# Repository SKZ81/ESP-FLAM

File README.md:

This is branch **master** (normal operation firmware)

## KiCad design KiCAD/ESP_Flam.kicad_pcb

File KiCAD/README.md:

# ESP FLAM PCB

## Top Layer

## Bottom Layer

## 3D View

## Real Board

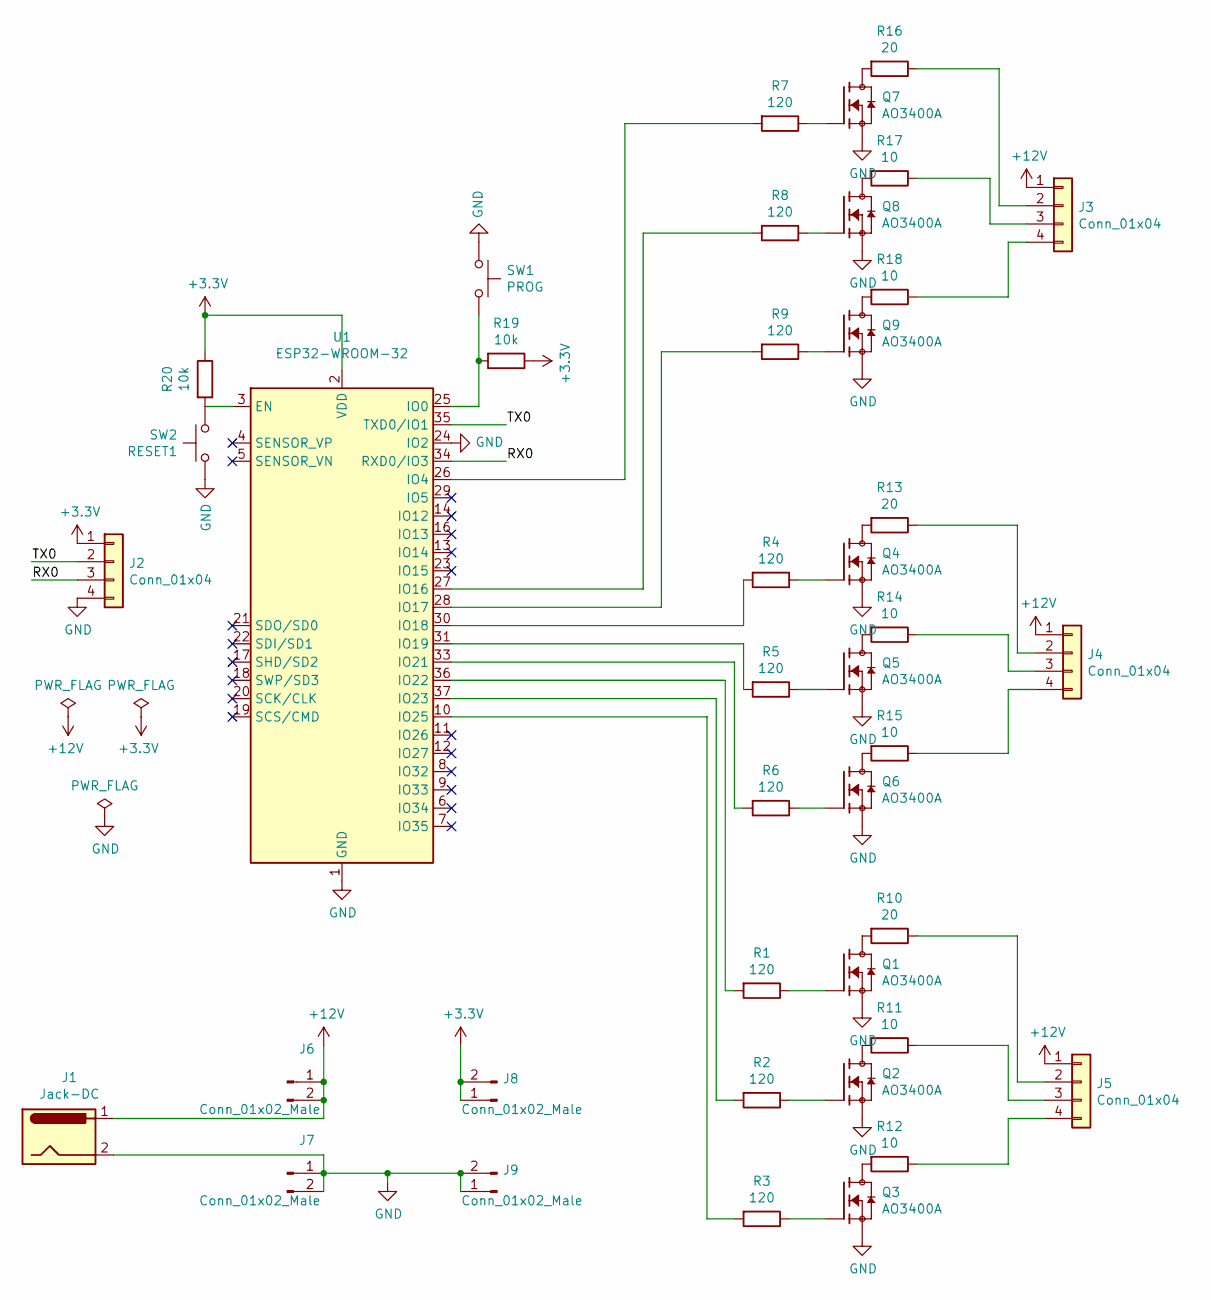
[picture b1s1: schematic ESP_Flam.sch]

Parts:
J1: Jack-DC; BarrelJack_CUI_PJ-063AH_Horizontal
J2, J3, J4, J5: Conn_01x04; PinHeader_1x04_P2.54mm_Vertical
J6, J7, J8, J9: Conn_01x02_Male; PinHeader_1x02_P2.54mm_Vertical
Q1, Q2, Q3, Q4, Q5, Q6, Q7, Q8, Q9: AO3400A; SOT95P280X125-3N; LCSC Part C347475
R1, R2, R3, R4, R5, R6, R7, R8, R9: 120; R_0805_2012Metric; LCSC Part C17437
R10, R13, R16: 20; R_Axial_DIN0414_L11.9mm_D4.5mm_P15.24mm_Horizontal
R11, R12, R14, R15, R17, R18: 10; R_Axial_DIN0414_L11.9mm_D4.5mm_P15.24mm_Horizontal
R19, R20: 10k; R_0805_2012Metric; LCSC Part C17414
RESET1: SW2; SW_PUSH_6mm
SW1: PROG; SW_PUSH_6mm
U1: ESP32-WROOM-32

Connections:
+3V3: J2.1, J8.1, J8.2, R19.1, R20.1, U1.2 (VDD)
+12V: J1.1, J3.1, J4.1, J5.1, J6.1, J6.2
/RX0: J2.3, U1.34 (RXD0/IO3)
/TX0: J2.2, U1.35 (TXD0/IO1)
GND: J1.2, J2.4, J7.1, J7.2, J9.1, J9.2, Q1.2 (S), Q2.2 (S), Q3.2 (S), Q4.2 (S), Q5.2 (S), Q6.2 (S), Q7.2 (S), Q8.2 (S), Q9.2 (S), RESET1.1, SW1.1, U1.1 (GND), U1.15 (GND), U1.24 (IO2), U1.38 (GND), U1.39 (GND)
unnamed: J3.2, R16.1
unnamed: J3.3, R17.1
unnamed: J3.4, R18.1
unnamed: J4.2, R13.1
unnamed: J4.3, R14.1
unnamed: J4.4, R15.1
unnamed: J5.2, R10.1
unnamed: J5.3, R11.1
unnamed: J5.4, R12.1
unnamed: Q1.1 (G), R1.1
unnamed: Q1.3 (D), R10.2
unnamed: Q2.1 (G), R2.1
unnamed: Q2.3 (D), R11.2
unnamed: Q3.1 (G), R3.1
unnamed: Q3.3 (D), R12.2
unnamed: Q4.1 (G), R4.1
unnamed: Q4.3 (D), R13.2
unnamed: Q5.1 (G), R5.1
unnamed: Q5.3 (D), R14.2
unnamed: Q6.1 (G), R6.1
unnamed: Q6.3 (D), R15.2
unnamed: Q7.1 (G), R7.1
unnamed: Q7.3 (D), R16.2
unnamed: Q8.1 (G), R8.1
unnamed: Q8.3 (D), R17.2
unnamed: Q9.1 (G), R9.1
unnamed: Q9.3 (D), R18.2
unnamed: R1.2, U1.36 (IO22)
unnamed: R2.2, U1.37 (IO23)
unnamed: R3.2, U1.10 (IO25)
unnamed: R4.2, U1.30 (IO18)
unnamed: R5.2, U1.31 (IO19)
unnamed: R6.2, U1.33 (IO21)
unnamed: R7.2, U1.26 (IO4)
unnamed: R8.2, U1.27 (IO16)
unnamed: R9.2, U1.28 (IO17)
unnamed: R19.2, SW1.2, U1.25 (IO0)
unnamed: R20.2, RESET1.2, U1.3 (EN)

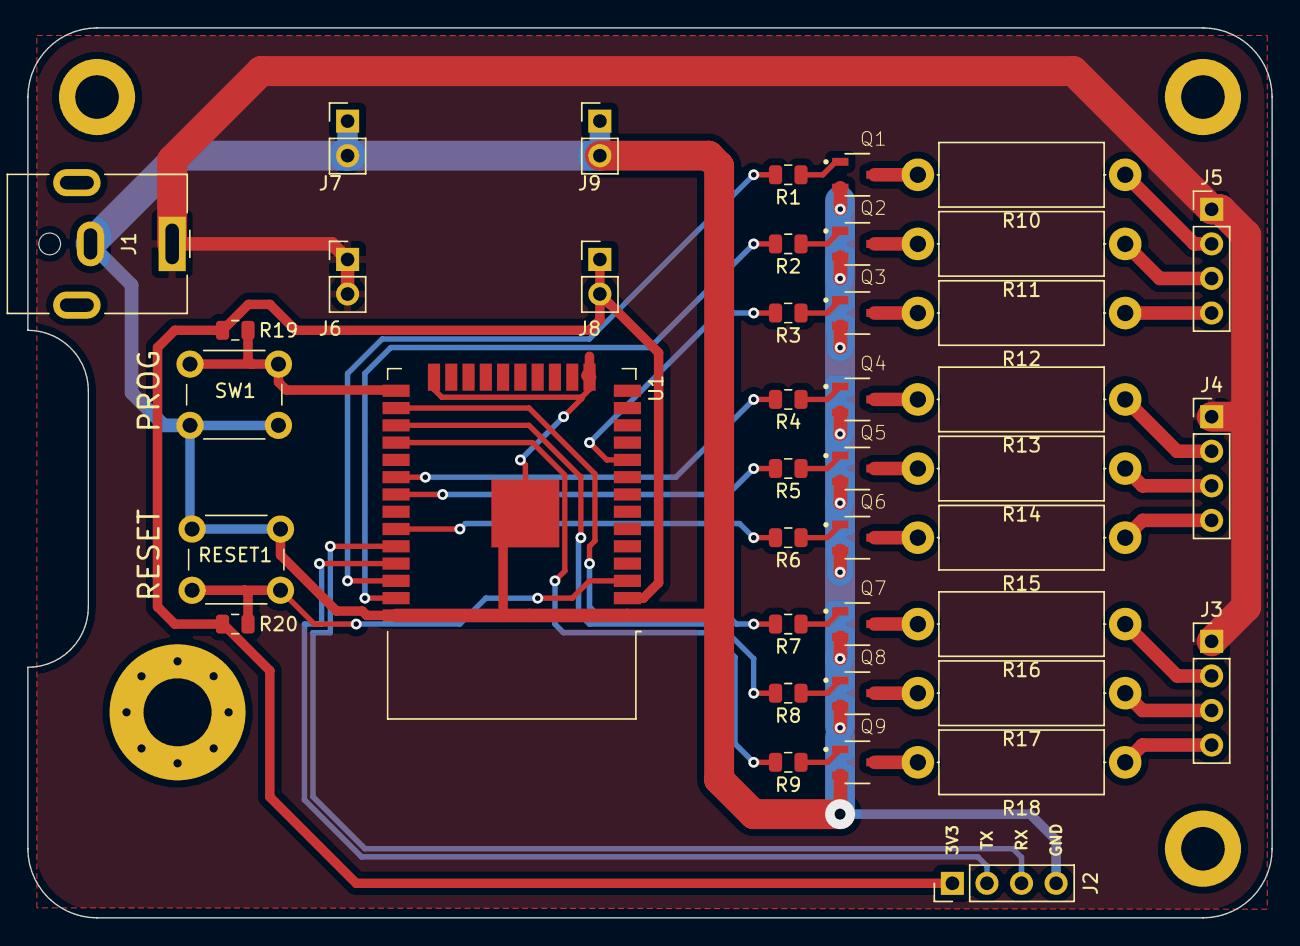
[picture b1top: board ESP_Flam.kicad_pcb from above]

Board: 2 copper layers, 91.4 x 65.4 mm, 44 parts (0 on the bottom side), 43 nets.

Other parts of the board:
 : MountingHole_3.2mm_M3_DIN965_Pad
 #2,  #3: MountingHole_3.2mm_M3_DIN965_Pad

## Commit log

2020-11-16 Added illustration
2020-12-01 Reorganized source tree
2020-12-01 Added test esp-idf SDK firmware
2020-12-01 changed test FW dir name
2020-12-03 test FW becomes rather a branch
2020-12-03 Updated README, say which branch it is
2020-12-03 Master branch : 'spawn'/fork from test-FW branch
2020-12-03 Added Mode Management unit
    Defines basic mode configuration structure
2020-12-03 Added baby 'Mode Manager'
    It haz :
    * a 'full-featured" fire effect
    * a blink effect (errors, connection to WiFi...)
    * A basic Web API (POST /fire and POST /firestop)
    * POST /fire takes a JSON with brightness, flickering, speed parameters
    * brightness is a multiplucation factor (% 0..1)
2020-12-19 test HTML/JS HSV/HSL rotations
2020-12-19 Added fire effect control panel
2020-12-19 Added fire effect URL and few improvements
2020-12-19 fire effect: mode_mngt
2020-12-21 Added color space (RGB, HSV, HSL) functions
2020-12-21 Added boot animation
    Introduces single handle for all modes
2020-12-21 Added color_space unit to build list
2020-12-21 Added boot animation in main
2020-12-21 Added static IP management.
    THIS COMMIT REQUIRES UPGRADING TO ESP-IDF 4.2
    $ git checkout v4.2
    $ git submodule update --init --recursive
2020-12-31 Remove silly duty cycle test value
2020-12-31 color_spaces.c: embetter log
2020-12-31 Embetter HTML page
2020-12-31 double -> float (esp32's FPU handle them 10x faster)
    See (for instance) : https://github.com/espressif/arduino-esp32/issues/2538#issuecomment-490462322
2020-12-31 Fixed Mode checking
2020-12-31 More realistic fire effect
    - Don't integrate deltas, it leads to unrealistic effect
    - Take the yellow_factor sent by the HTML into account
2020-12-31 Better Boot Animation
2020-12-31 Added images & README for PCB
